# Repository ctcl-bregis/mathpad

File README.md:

# MathPad "Fort Myers"

MathPad was an idea to recreate HP's CalcPad device with modern components and design. The codename "Fort Myers" was chosen because the entire project was designed during the business trip to the Fort Myers area for work in Fort Myers Beach. The device was developed with the idea of that it would be used with the Xactimate estimating software.

The project was the first of CTCL's circuit design projects to reach the assembly stage; PCB and components ordered and received.

The project was likely abandoned in December 2022 due to the lack of equipment and skills required to solder the tiny, delicate components. The project was officially canceled on January 19, 2024 after the introduction of an off-the-shelf product, the Logitech G600 MMO mouse into my workflow in January 2023. This project was made with the idea of necessity as I was expected to start having to use Xactimate after the conclusion of the business trip.

On January 19, 2024, I released whatever work I had done for the project. The existing components ordered may be reused for other projects.

## Files
Included in the "hw" directory is all of the hardware files exported from EasyEDA.

No firmware has been developed for the device

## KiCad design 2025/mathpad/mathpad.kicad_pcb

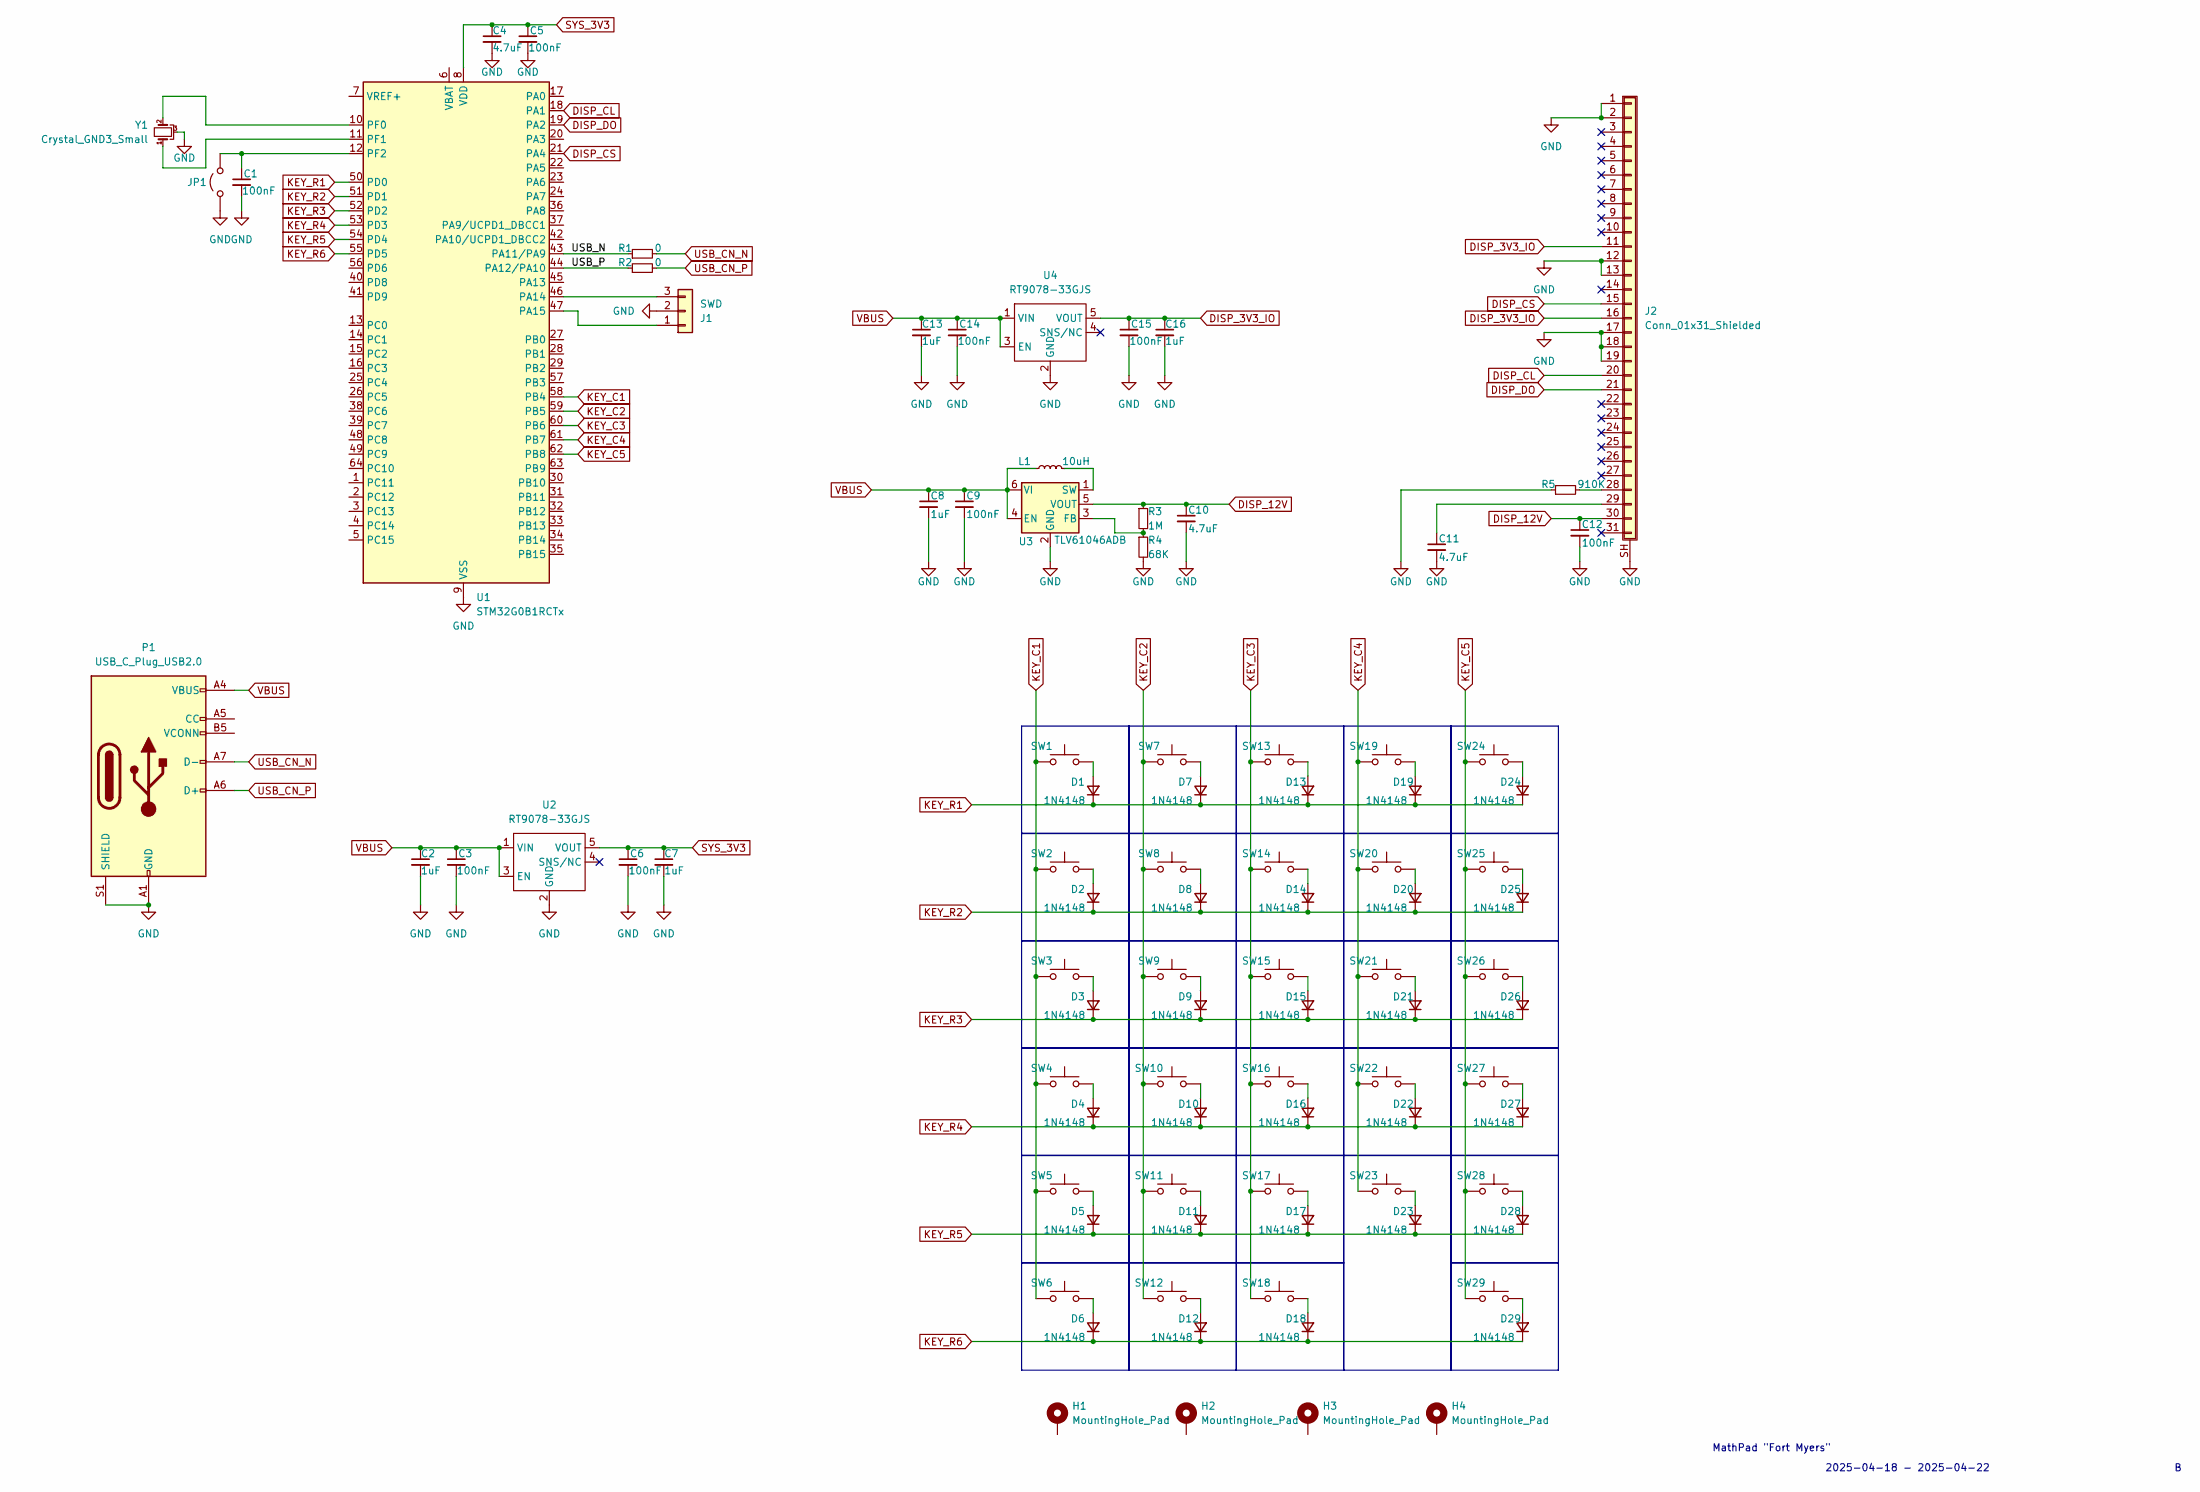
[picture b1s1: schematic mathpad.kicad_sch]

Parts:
C1, C3, C5, C6, C9, C12, C14, C15: 100nF; C_0603_1608Metric
C2, C7, C8, C13, C16: 1uF; C_0603_1608Metric
C4, C10, C11: 4.7uF; C_1206_3216Metric
D1, D2, D3, D4, D5, D6, D7, D8, D9, D10, D11, D12, D13, D14, D15, D16, D17, D18, D19, D20, D21, D22, D23, D24, D25, D26, D27, D28, D29: 1N4148; D_DO-35_SOD27_P7.62mm_Horizontal
H1, H2, H3, H4: MountingHole_Pad; MountingHole_2.2mm_M2_Pad
J1: SWD; PinHeader_1x03_P2.54mm_Vertical
J2: Conn_01x31_Shielded; TE_3-1734839-1_1x31-1MP_P0.5mm_Horizontal
JP1: Jumper_2_Open; SolderJumper-2_P1.3mm_Open_Pad1.0x1.5mm
L1: 10uH; L_Taiyo-Yuden_MD-5050
P1: USB_C_Plug_USB2.0; USB_C_Receptacle_G-Switch_GT-USB-7010ASV
R1, R2: 0; R_0603_1608Metric
R3: 1M; R_0603_1608Metric
R4: 68K; R_0603_1608Metric
R5: 910K; R_0603_1608Metric
SW1, SW2, SW3, SW4, SW5, SW6, SW7, SW8, SW9, SW10, SW11, SW12, SW13, SW14, SW15, SW16, SW17, SW18, SW19, SW20, SW21, SW22, SW23, SW24, SW25, SW26, SW27, SW28, SW29: SW_Push; SW_Cherry_MX_1.00u_PCB
U1: STM32G0B1RCTx; LQFP-64_10x10mm_P0.5mm
U2, U4: RT9078-33GJS; TSOT-23-5
U3: TLV61046ADB; SOT-23-6
Y1: Crystal_GND3_Small; Resonator_SMD_Murata_CSTCR_4.5x2x1.15mm

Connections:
/USB_N: R1.1, U1.43 (PA11/PA9)
/USB_P: R2.1, U1.44 (PA12/PA10)
DISP_3V3_IO: C15.1, C16.1, J2.11, J2.16, U4.5 (VOUT)
DISP_12V: C10.1, C12.1, J2.30, R3.1, U3.5 (VOUT)
DISP_CL: J2.20, U1.18 (PA1)
DISP_CS: J2.15, U1.21 (PA4)
DISP_DO: J2.21, U1.19 (PA2)
GND: C1.2, C2.2, C3.2, C4.2, C5.2, C6.2, C7.2, C8.2, C9.2, C10.2, C11.2, C12.2, C13.2, C14.2, C15.2, C16.2, J1.2, J2.1, J2.2, J2.12, J2.13, J2.17, J2.18, J2.19, J2.SH (Shield), JP1.2 (B), P1.A1 (GND), P1.A12 (GND), P1.B1 (GND), P1.B12 (GND), P1.S1 (SHIELD), R4.2, R5.1, U1.9 (VSS), U2.2 (GND), U3.2 (GND), U4.2 (GND), Y1.3
KEY_C1: SW1.1, SW2.1, SW3.1, SW4.1, SW5.1, SW6.1, U1.58 (PB4)
KEY_C2: SW7.1, SW8.1, SW9.1, SW10.1, SW11.1, SW12.1, U1.59 (PB5)
KEY_C3: SW13.1, SW14.1, SW15.1, SW16.1, SW17.1, SW18.1, U1.60 (PB6)
KEY_C4: SW19.1, SW20.1, SW21.1, SW22.1, SW23.1, U1.61 (PB7)
KEY_C5: SW24.1, SW25.1, SW26.1, SW27.1, SW28.1, SW29.1, U1.62 (PB8)
KEY_R1: D1.1 (K), D7.1 (K), D13.1 (K), D19.1 (K), D24.1 (K), U1.50 (PD0)
KEY_R2: D2.1 (K), D8.1 (K), D14.1 (K), D20.1 (K), D25.1 (K), U1.51 (PD1)
KEY_R3: D3.1 (K), D9.1 (K), D15.1 (K), D21.1 (K), D26.1 (K), U1.52 (PD2)
KEY_R4: D4.1 (K), D10.1 (K), D16.1 (K), D22.1 (K), D27.1 (K), U1.53 (PD3)
KEY_R5: D5.1 (K), D11.1 (K), D17.1 (K), D23.1 (K), D28.1 (K), U1.54 (PD4)
KEY_R6: D6.1 (K), D12.1 (K), D18.1 (K), D29.1 (K), U1.55 (PD5)
unnamed: D1.2 (A), SW1.2
unnamed: D2.2 (A), SW2.2
unnamed: D3.2 (A), SW3.2
unnamed: D4.2 (A), SW4.2
unnamed: D5.2 (A), SW5.2
unnamed: D6.2 (A), SW6.2
unnamed: D7.2 (A), SW7.2
unnamed: D8.2 (A), SW8.2
unnamed: D9.2 (A), SW9.2
unnamed: D10.2 (A), SW10.2
unnamed: D11.2 (A), SW11.2
unnamed: D12.2 (A), SW12.2
unnamed: D13.2 (A), SW13.2
unnamed: D14.2 (A), SW14.2
unnamed: D15.2 (A), SW15.2
unnamed: D16.2 (A), SW16.2
unnamed: D17.2 (A), SW17.2
unnamed: D18.2 (A), SW18.2
unnamed: D19.2 (A), SW19.2
unnamed: D20.2 (A), SW20.2
unnamed: D21.2 (A), SW21.2
unnamed: D22.2 (A), SW22.2
unnamed: D23.2 (A), SW23.2
unnamed: D24.2 (A), SW24.2
unnamed: D25.2 (A), SW25.2
unnamed: D26.2 (A), SW26.2
unnamed: D27.2 (A), SW27.2
unnamed: D28.2 (A), SW28.2
unnamed: D29.2 (A), SW29.2
unnamed: J1.1, U1.47 (PA15)
unnamed: J1.3, U1.46 (PA14)
unnamed: J2.28, R5.2
unnamed: C11.1, J2.29
unnamed: C1.1, JP1.1 (A), U1.12 (PF2)
unnamed: U1.10 (PF0), Y1.2
unnamed: U1.11 (PF1), Y1.1
unnamed: R3.2, R4.1, U3.3 (FB)
unnamed: L1.2, U3.1 (SW)
SYS_3V3: C4.1, C5.1, C6.1, C7.1, U1.8 (VDD), U2.5 (VOUT)
USB_CN_N: P1.A7 (D-), R1.2
USB_CN_P: P1.A6 (D+), R2.2
VBUS: C2.1, C3.1, C8.1, C9.1, C13.1, C14.1, L1.1, P1.A4 (VBUS), P1.A9 (VBUS), P1.B4 (VBUS), P1.B9 (VBUS), U2.1 (VIN), U2.3 (EN), U3.4 (EN), U3.6 (VI), U4.1 (VIN), U4.3 (EN)

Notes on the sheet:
MathPad "Fort Myers"
2025-04-18 - 2025-04-22

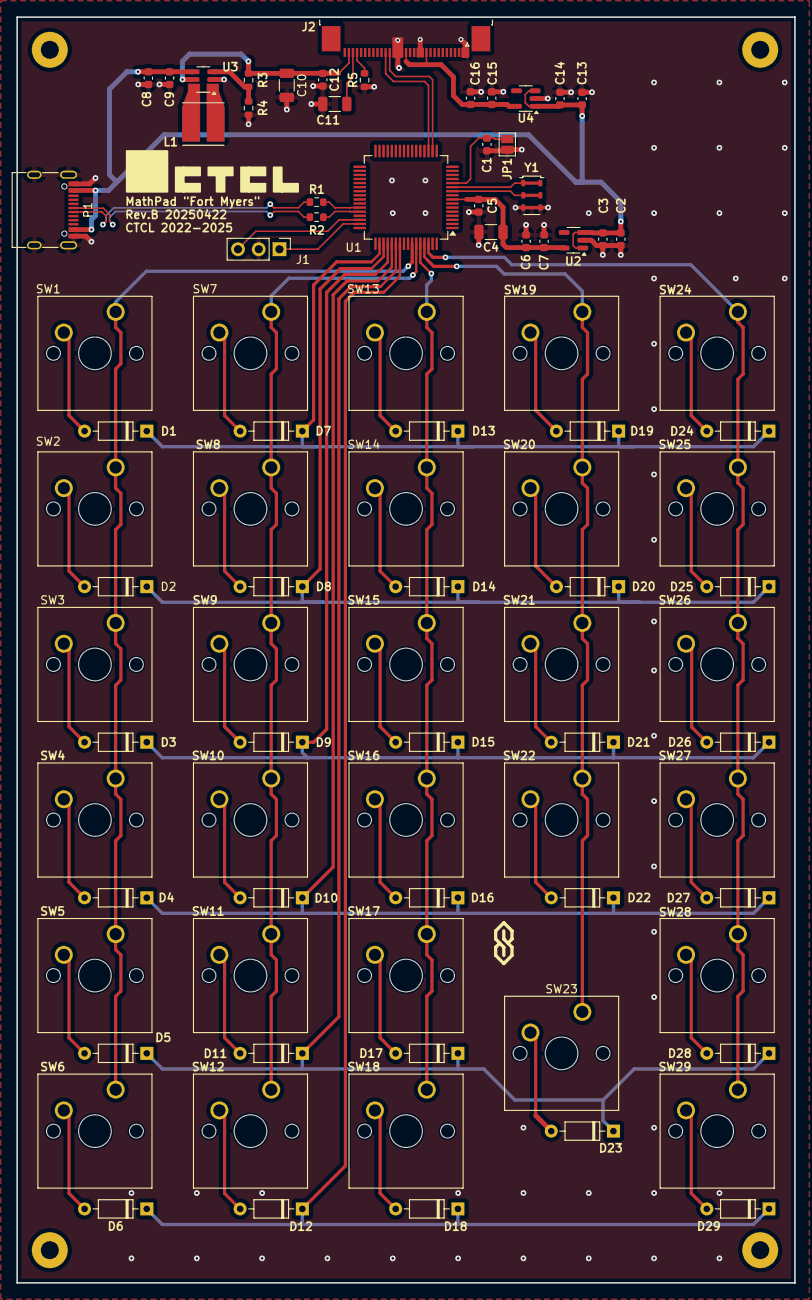
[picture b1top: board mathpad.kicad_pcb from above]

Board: 4 copper layers, 95.2 x 155.0 mm, 93 parts (0 on the bottom side), 61 nets.

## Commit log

2024-01-19 add BOM
2025-04-18 20250418-1
2025-04-22 20250422-1
2025-04-23 20250423-1
